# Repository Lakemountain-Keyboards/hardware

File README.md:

<div align="center">

  # Lakemountain Keyboards

  Hardware Repository

  Kicad Schematic & PCB layout

</div>

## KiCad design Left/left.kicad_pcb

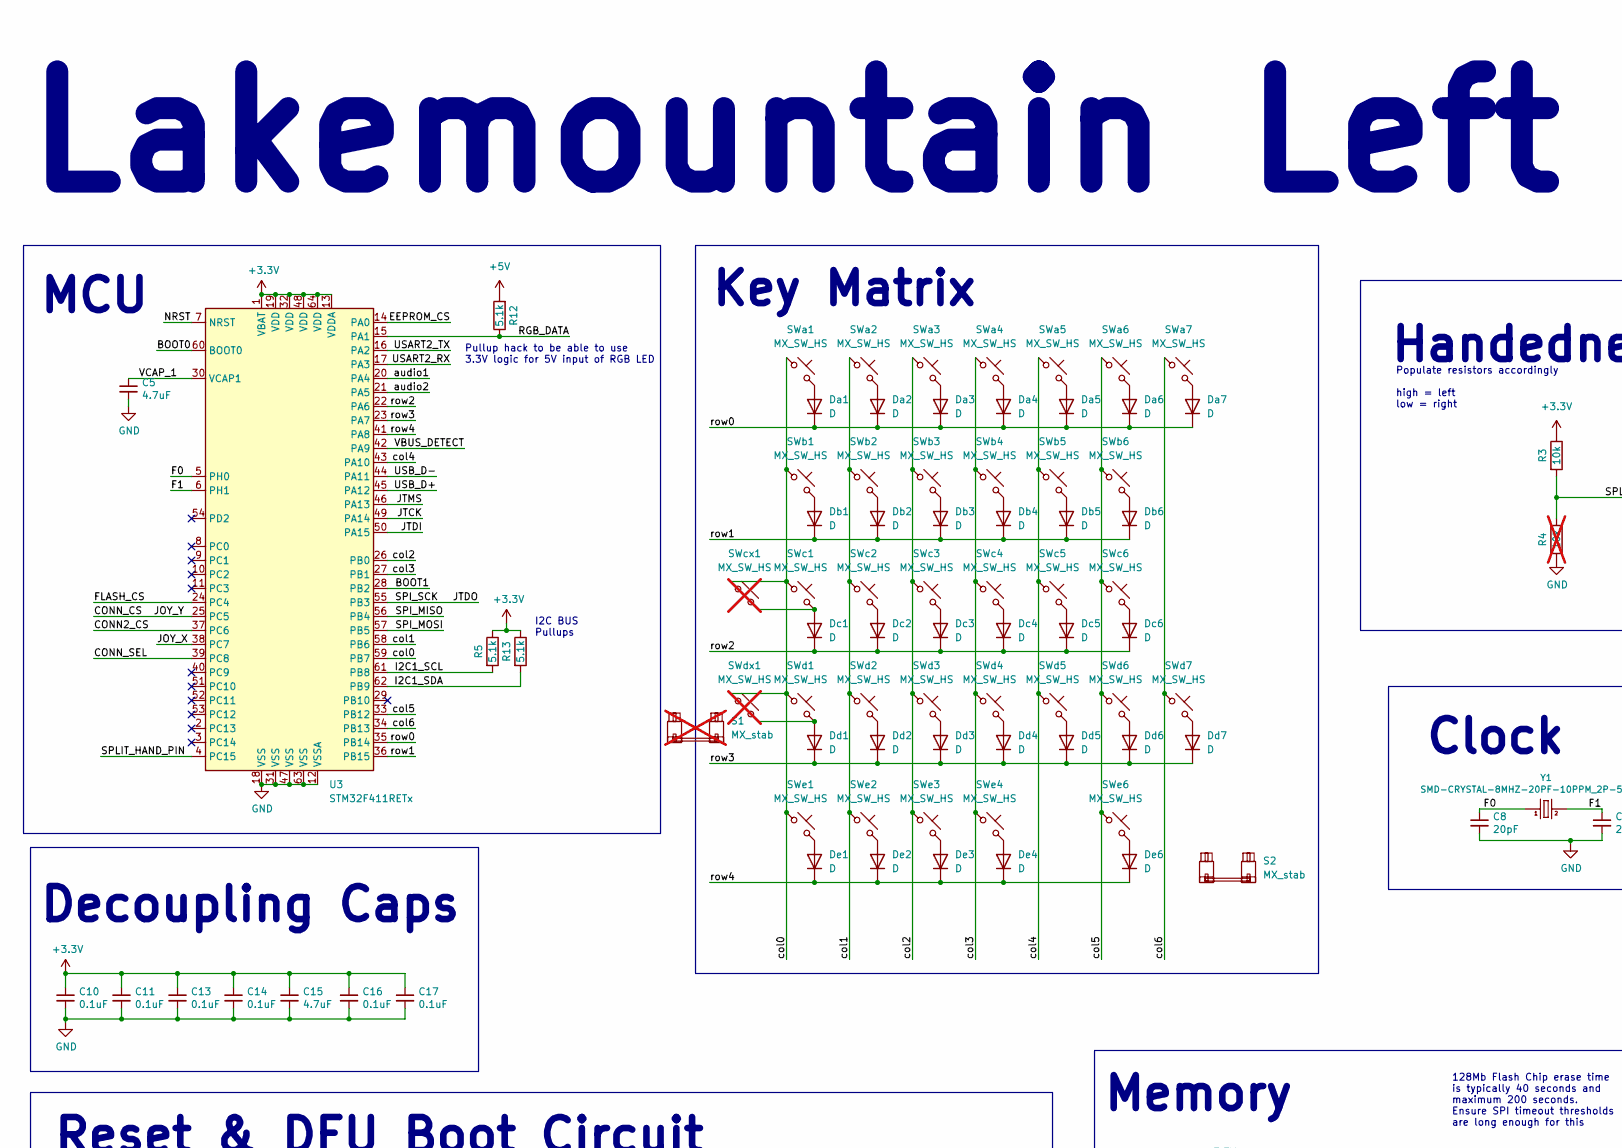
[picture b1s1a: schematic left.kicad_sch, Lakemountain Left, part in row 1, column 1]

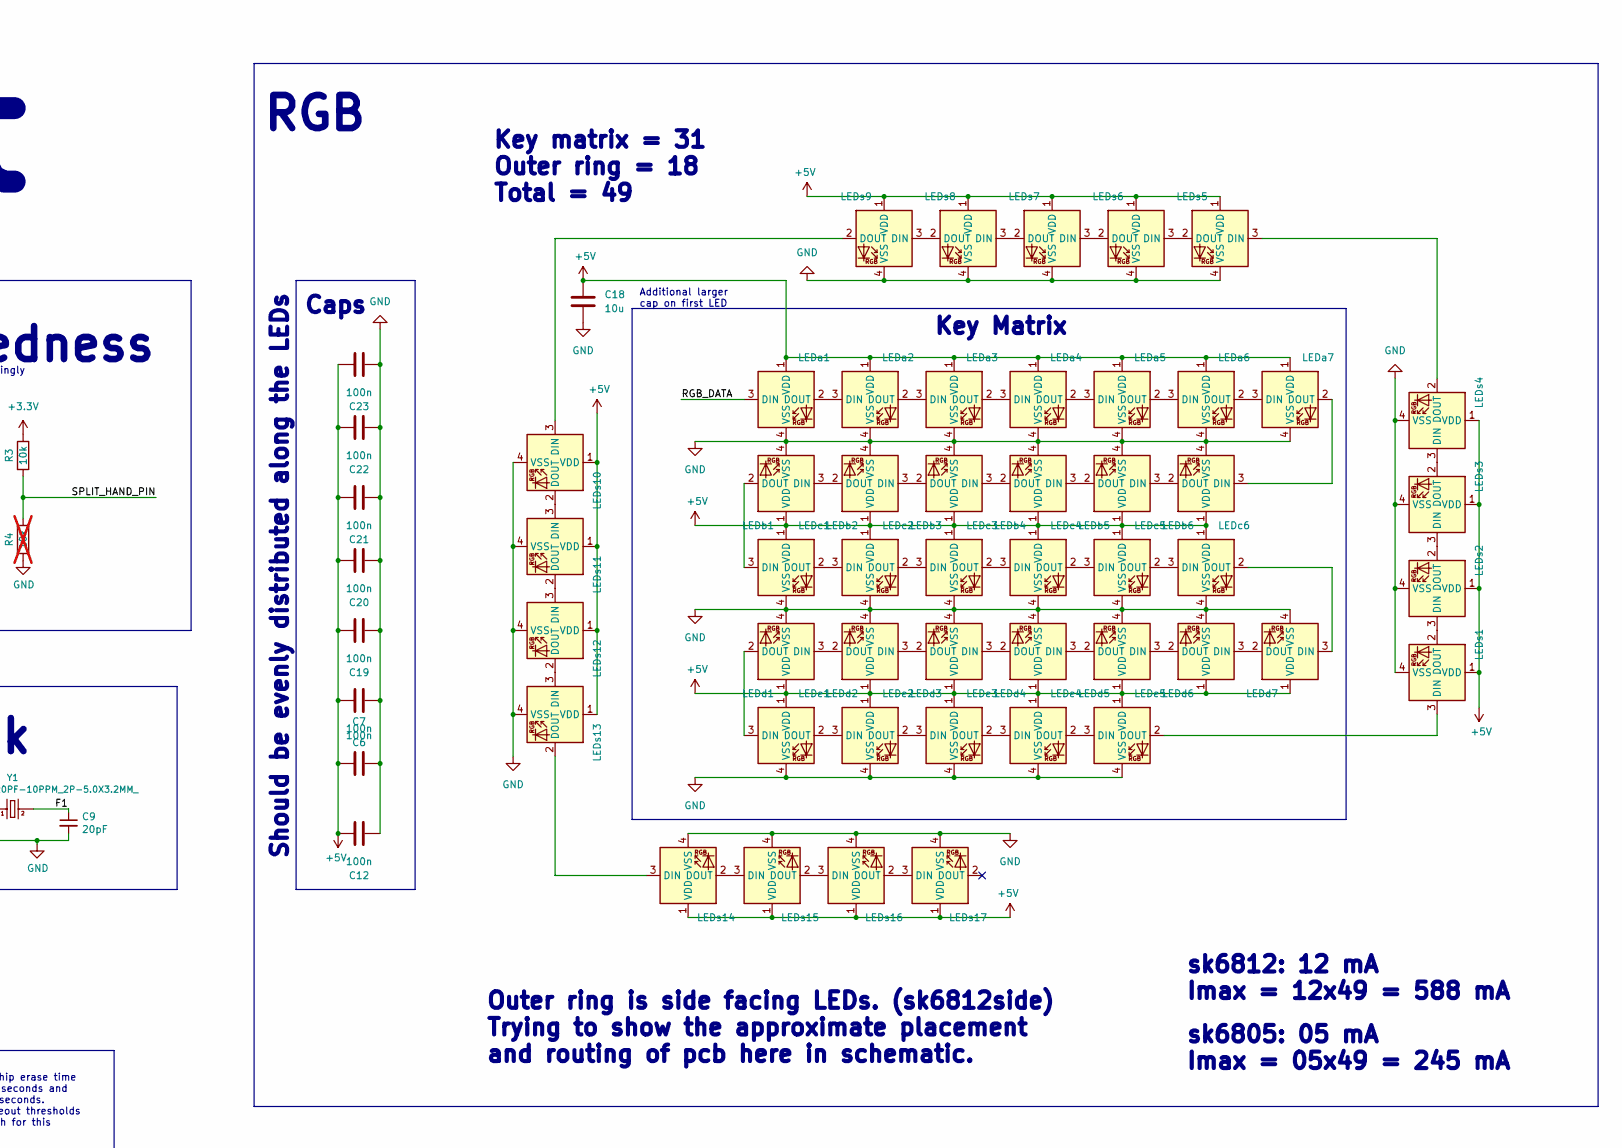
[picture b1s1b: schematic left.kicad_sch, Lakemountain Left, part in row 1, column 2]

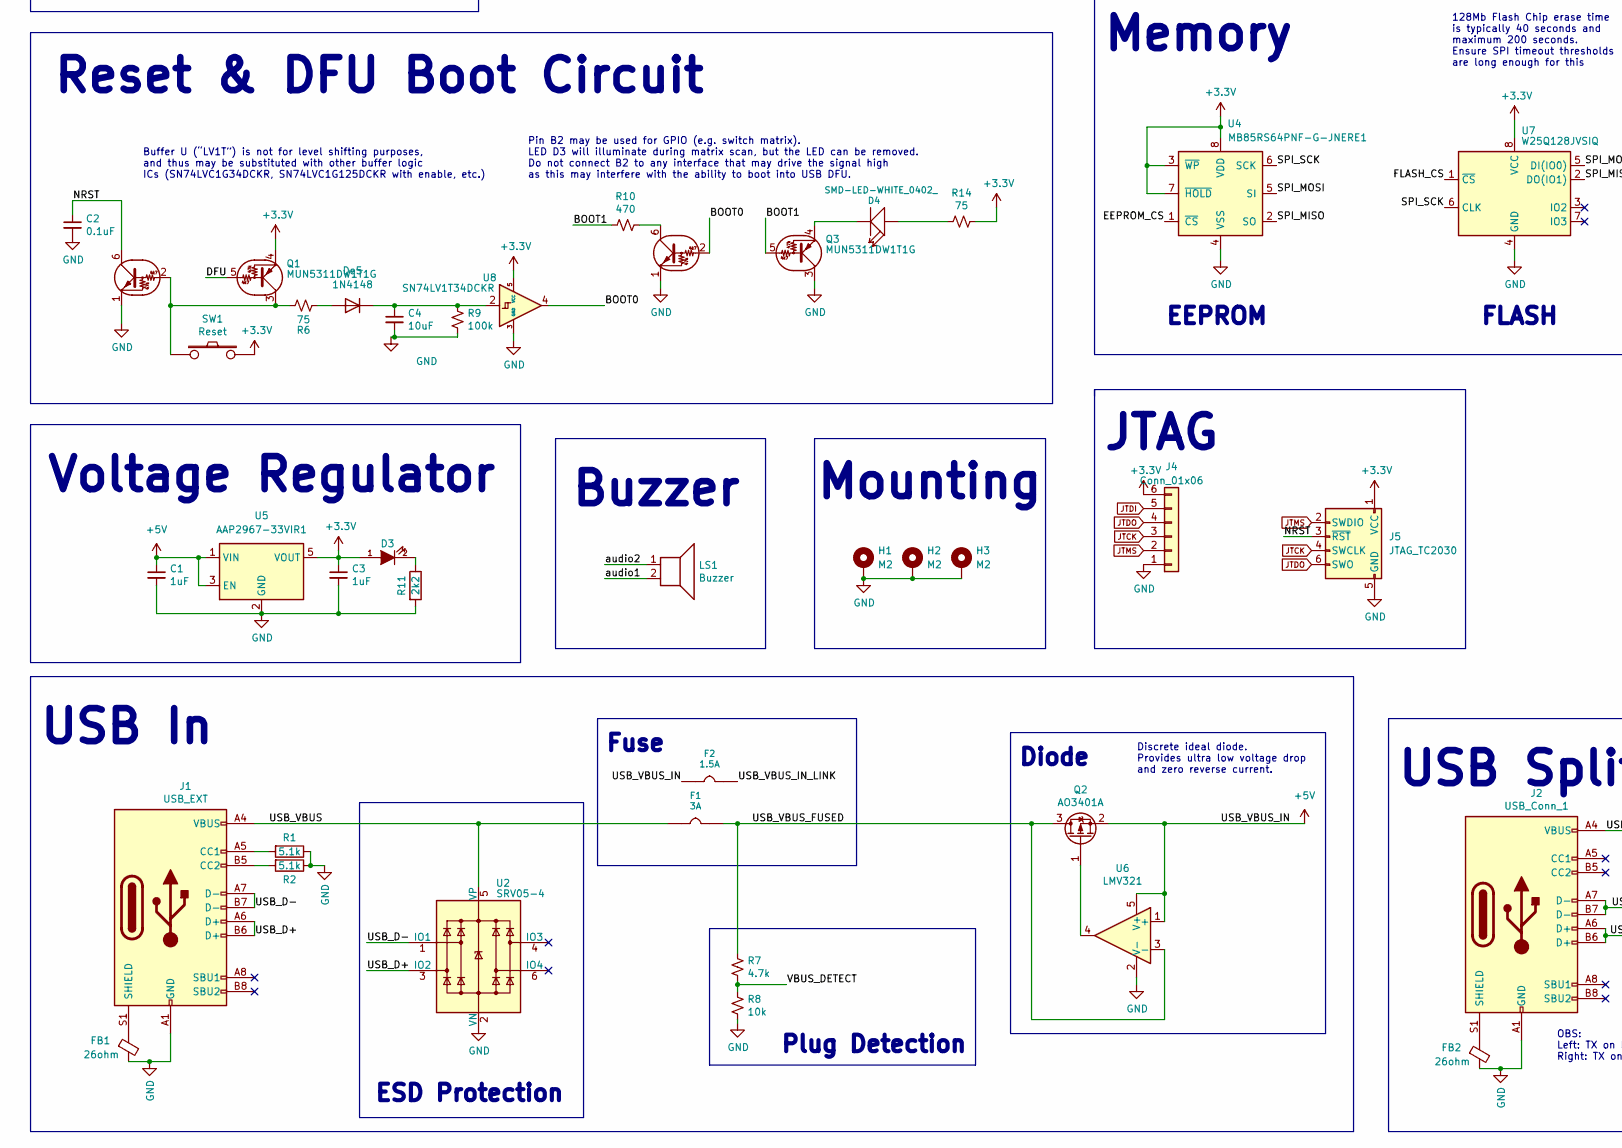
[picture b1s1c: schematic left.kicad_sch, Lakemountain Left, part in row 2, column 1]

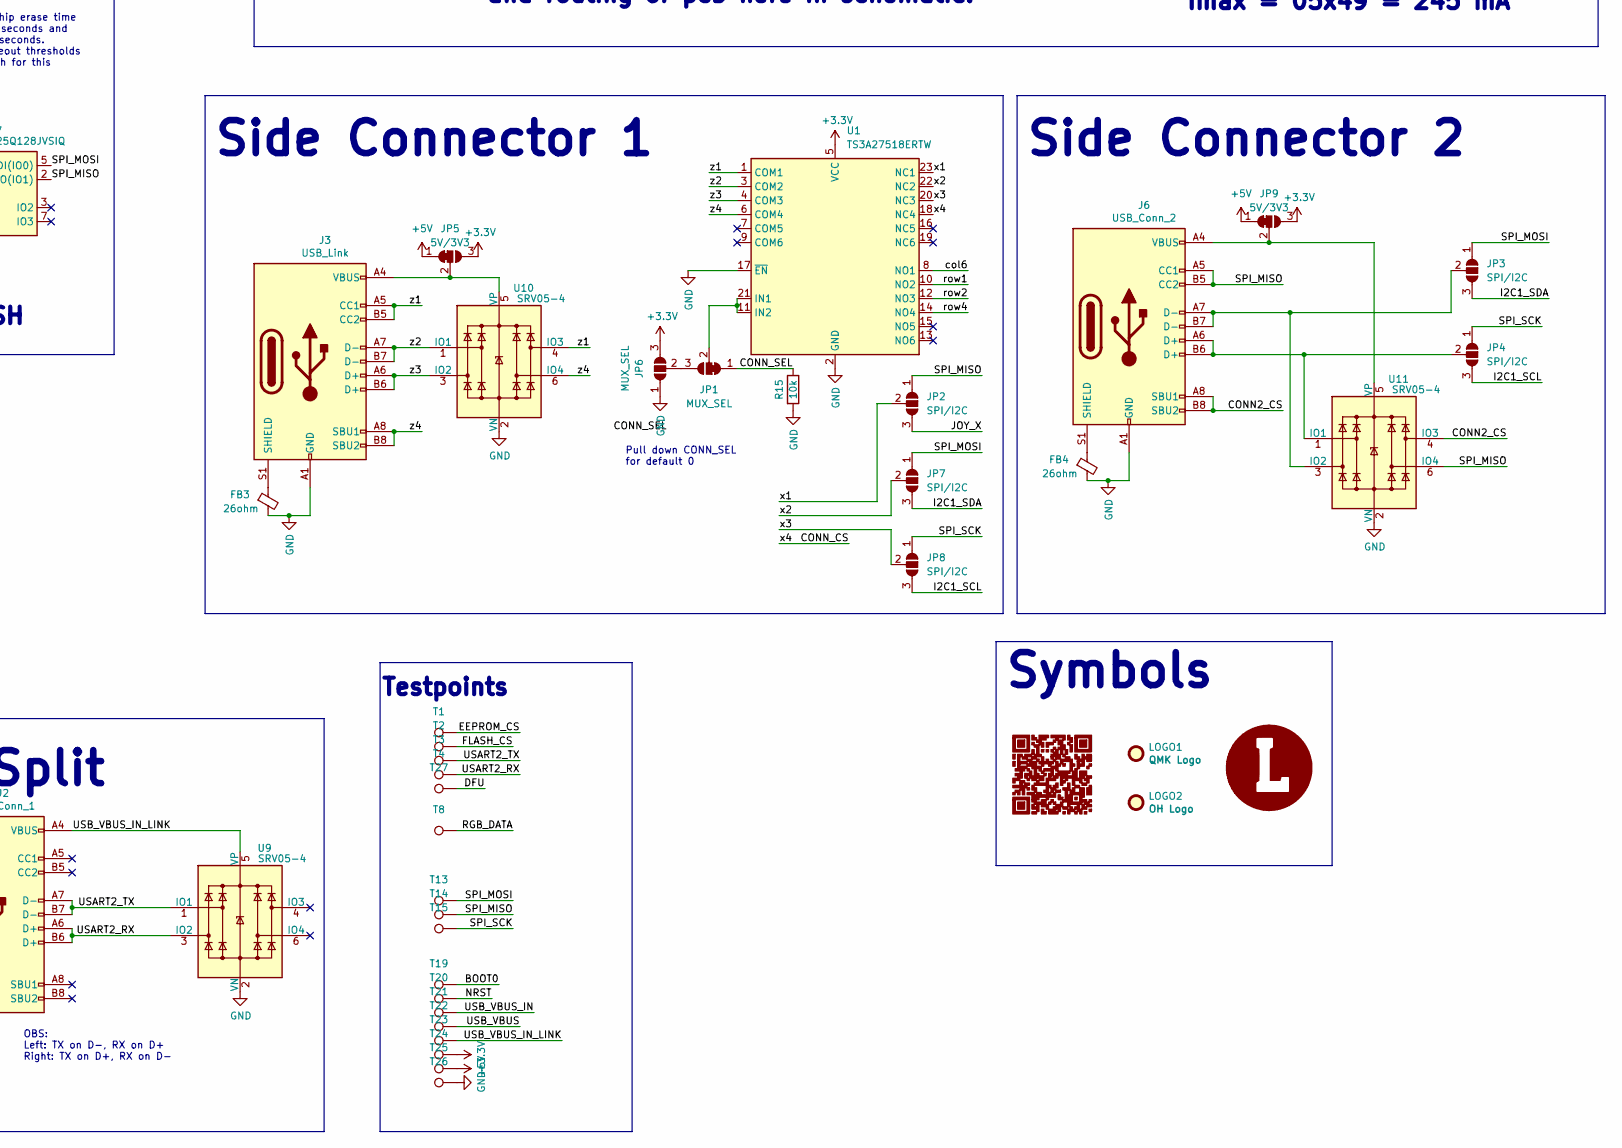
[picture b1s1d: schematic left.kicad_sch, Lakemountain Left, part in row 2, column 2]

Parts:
C1, C3: cap_1uF_10v_0402; C_0402_1005Metric; MPN CC0402KRX5R6BB105; LCSC C52923
C2, C10, C11, C13, C14, C16, C17: cap_100nF_16v_0402; C_0402_1005Metric; MPN CL05B104KO5NNNC; LCSC C1525
C4: cap_10uF_10v_0402; C_0402_1005Metric; MPN CL10A106KP8NNNC; LCSC C19702
C5, C15: cap_4.7uF_10v_0402; C_0402_1005Metric; MPN CL05A475MP5NRNC; LCSC C23733
C6, C7, C12, C19, C20, C21, C22, C23: 100n; C_0805; LCSC C495959
C8, C9: cap_20pF_50v_0402; C_0402_1005Metric; MPN 0402CG200J500NT; LCSC C1554
C18: 10u; C_0805; LCSC C90544
D3: LED; LED_0603_1608Metric; LCSC Part C72041
D4: SMD-LED-WHITE_0402_; LED_0402; MPN 16-219A/T2D-AR2T1QY/3T; LCSC C74342
Da1, Da2, Da3, Da4, Da5, Da6, Da7: D; D_SOD-123; LCSC C81598
Db1, Db2, Db3, Db4, Db5, Db6: D; D_SOD-123; LCSC C81598
Dc1, Dc2, Dc3, Dc4, Dc5, Dc6: D; D_SOD-123; LCSC C81598
Dd1, Dd2, Dd3, Dd4, Dd5, Dd6, Dd7: D; D_SOD-123; LCSC C81598
De1, De2, De3, De4, De6: D; D_SOD-123; LCSC C81598
De5: 1N4148; D_SOD-523; LCSC C68948
F1: 3A; F1206; MPN SMD0805-050; LCSC C89656
F2: 1.5A; F1206; MPN SMD0805-050; LCSC C89655
FB1, FB2, FB3, FB4: fb_0402_26ohm; R_0402_1005Metric; MPN CBG100505U260T; LCSC C668229
H1, H2, H3: M2; MountingHole_2.2mm_M2_Pad_Via
J1: USB_EXT; USB_C_Receptacle_HRO_TYPE-C-31-M-12; Mouser C165948
J2: USB_Conn_1; USB_C_Receptacle_HRO_TYPE-C-31-M-12; Mouser C165948
J3: USB_Link; USB_C_Receptacle_HRO_TYPE-C-31-M-12; Mouser C165948
J4: Conn_01x06; PinHeader_1x06_P2.54mm_Vertical
J5: JTAG_TC2030; CON_TC2030_outlined
J6: USB_Conn_2; USB_C_Receptacle_HRO_TYPE-C-31-M-12; Mouser C165948
JP1: MUX_SEL; SolderJumper-3_P1.3mm_Bridged12_RoundedPad1.0x1.5mm
JP2, JP3, JP4, JP7, JP8: SPI/I2C; SolderJumper-3_P1.3mm_Open_RoundedPad1.0x1.5mm_NumberLabels
JP5, JP9: 5V/3V3; SolderJumper-3_P1.3mm_Bridged12_RoundedPad1.0x1.5mm
JP6: MUX_SEL; SolderJumper-3_P1.3mm_Open_RoundedPad1.0x1.5mm_NumberLabels
LEDa1, LEDa2, LEDa3, LEDa4, LEDa5, LEDa6, LEDa7: MX_SK6812MINI-E; LED_MX_6028R; LCSC C5149201
LEDb1, LEDb2, LEDb3, LEDb4, LEDb5, LEDb6: MX_SK6812MINI-E; LED_MX_6028R_Flipped; LCSC C5149201
LEDc1: MX_SK6812MINI-E; LED_MX_6028R_SOLO; LCSC C5149201
LEDc2, LEDc3, LEDc4, LEDc5, LEDc6: MX_SK6812MINI-E; LED_MX_6028R; LCSC C5149201
LEDd1, LEDd2: MX_SK6812MINI-E; LED_MX_6028R_SOLO; LCSC C5149201
LEDd3, LEDd4, LEDd5, LEDd6, LEDd7: MX_SK6812MINI-E; LED_MX_6028R_Flipped; LCSC C5149201
LEDe1, LEDe2, LEDe3, LEDe4, LEDe5: MX_SK6812MINI-E; LED_MX_6028R; LCSC C5149201
LEDs1, LEDs2, LEDs3, LEDs4, LEDs5, LEDs6, LEDs7, LEDs8, LEDs9, LEDs10, LEDs11, LEDs12, LEDs13, LEDs14, LEDs15, LEDs16, LEDs17: sk6812side; LCSC C2890037
LOGO1: QMK Logo; QMK_PoweredBy
LOGO2: OH Logo; OSHW-Logo2_9.8x8mm_SilkScreen
LS1: Buzzer; Buzzer_Mallory_AST1109MLTRQ; LCSC C201047
Q1, Q3: MUN5311DW1T1G; SOT-363_SC-70-6_SC-88; LCSC C152542
Q2: AO3401A; SOT-23; LCSC Part C15127
R1, R2, R5, R13: 5.1k; R_0603_1608Metric; Mouser C27834
R3, R15: 10k; R_0603_1608Metric; LCSC C25804
R4: 10k; R_0603_1608Metric; LCSC C25804; not fitted
R6, R14: r_75_0402_1p; R_0402_1005Metric; MPN 0402WGF750JTCE; LCSC C25133
R7: r_4.7k_0402_1p; R_0402_1005Metric; MPN 0402WGF4701TCE; LCSC C25900
R8: r_10k_0402_1p; R_0402_1005Metric; MPN 0402WGF1002TCE; LCSC C25744
R9: r_100k_0402_1p; R_0402_1005Metric; MPN 0402WGF1003TCE; LCSC C25741
R10: r_470_0402_1p; R_0402_1005Metric; MPN 0402WGF4700TCE; LCSC C25117
R11: 2k2; R_0603_1608Metric; LCSC C4190
R12: 5.1k; R_0805_2012Metric_Pad1.20x1.40mm_HandSolder; Mouser C27834
S1: MX_stab; STAB_MX_P_2.25u; JLCPCB BOM 0; not fitted
S2: MX_stab; STAB_MX_P_2.25u; JLCPCB BOM 0
SW1: Reset; SW_SPST_TL3342; Mouser C318884
SWa1, SWa2, SWa3, SWa4, SWa5, SWa6, SWa7: MX_SW_HS; SW_MX_HS_1u; LCSC C2803348
SWb1: MX_SW_HS; SW_MX_HS_1.5u; LCSC C2803348
SWb2, SWb3, SWb4, SWb5, SWb6: MX_SW_HS; SW_MX_HS_1u; LCSC C2803348
SWc1: MX_SW_HS; SW_MX_HS_1.75u; LCSC C2803348
SWc2, SWc3, SWc4, SWc5, SWc6: MX_SW_HS; SW_MX_HS_1u; LCSC C2803348
SWcx1: MX_SW_HS; SW_MX_HS_1.75u_stp; LCSC C2803348; not fitted
SWd1: MX_SW_HS; SW_MX_HS_1.25u; LCSC C2803348
SWd2, SWd3, SWd4, SWd5, SWd6, SWd7: MX_SW_HS; SW_MX_HS_1u; LCSC C2803348
SWdx1: MX_SW_HS; SW_MX_HS_2.25u; LCSC C2803348; not fitted
SWe1, SWe2, SWe3, SWe4: MX_SW_HS; SW_MX_HS_1.25u; LCSC C2803348
SWe6: MX_SW_HS; SW_MX_HS_2.25u; LCSC C2803348
T1, T2, T3, T4, T8, T13, T14, T15, T19, T20, T21, T22, T23: TP; TestPoint_Pad_D1.0mm
T24: 3V3; TestPoint_Pad_D1.0mm
T25: 5V; TestPoint_Pad_D1.0mm
T26, T27: GND; TestPoint_Pad_D1.0mm
U1: TS3A27518ERTW; WQFN-24-1EP_4x4mm_P0.5mm_EP2.6x2.6mm; LCSC C2651937
U2, U9, U10, U11: SRV05-4; SOT-23-6; LCSC C85364
U3: STM32F411RETx; LQFP-64_10x10mm_P0.5mm
U4: MB85RS64PNF-G-JNERE1; SOP-8_3.9x4.9mm_P1.27mm; LCSC C8741
U5: AAP2967-33VIR1; SOT-23-5; LCSC C370742
U6: LMV321; SOT-23-5; JLCPCB BOM 1
U7: W25Q128JVSIQ; SOIC-8_5.23x5.23mm_P1.27mm; LCSC C97521
U8: SN74LV1T34DCKR; SOT-353_SC-70-5; LCSC C78541
Y1: SMD-CRYSTAL-8MHZ-20PF-10PPM_2P-5.0X3.2MM_; X2-SMD-5.0X3.2X1.3MM; MPN X50328MSB2GI; LCSC C115962

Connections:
+3.3V: C3.1, C10.1, C11.1, C13.1, C14.1, C15.1, C16.1, C17.1, D3.1 (A), J4.6, J5.1 (VCC), JP5.3 (B), JP6.3 (B), JP9.3 (B), Q1.4 (E), R3.1, R5.1, R13.1, R14.1, SW1.2, T24.1, U1.5 (VCC), U3.1 (VBAT), U3.13 (VDDA), U3.19 (VDD), U3.32 (VDD), U3.48 (VDD), U3.64 (VDD), U4.3 (~WP), U4.7 (~HOLD), U4.8 (VDD), U5.5 (VOUT), U7.8 (VCC), U8.5 (VCC)
+5V: C1.1, C6.1, C7.1, C12.1, C18.1, C19.1, C20.2, C21.1, C22.2, C23.1, F2.2, JP5.1 (A), JP9.1 (A), LEDa1.1 (VDD), LEDa2.1 (VDD), LEDa3.1 (VDD), LEDa4.1 (VDD), LEDa5.1 (VDD), LEDa6.1 (VDD), LEDa7.1 (VDD), LEDb1.1 (VDD), LEDb2.1 (VDD), LEDb3.1 (VDD), LEDb4.1 (VDD), LEDb5.1 (VDD), LEDb6.1 (VDD), LEDc1.1 (VDD), LEDc2.1 (VDD), LEDc3.1 (VDD), LEDc4.1 (VDD), LEDc5.1 (VDD), LEDc6.1 (VDD), LEDd1.1 (VDD), LEDd2.1 (VDD), LEDd3.1 (VDD), LEDd4.1 (VDD), LEDd5.1 (VDD), LEDd6.1 (VDD), LEDd7.1 (VDD), LEDe1.1 (VDD), LEDe2.1 (VDD), LEDe3.1 (VDD), LEDe4.1 (VDD), LEDe5.1 (VDD), LEDs1.1 (VDD), LEDs2.1 (VDD), LEDs3.1 (VDD), LEDs4.1 (VDD), LEDs5.1 (VDD), LEDs6.1 (VDD), LEDs7.1 (VDD), LEDs8.1 (VDD), LEDs9.1 (VDD), LEDs10.1 (VDD), LEDs11.1 (VDD), LEDs12.1 (VDD), LEDs13.1 (VDD), LEDs14.1 (VDD), LEDs15.1 (VDD), LEDs16.1 (VDD), LEDs17.1 (VDD), Q2.2 (S), R12.2, T21.1, T25.1, U5.1 (VIN), U5.3 (EN), U6.1 (+), U6.5 (V+)
/BOOT0: Q3.2 (B), T19.1, U3.60 (BOOT0), U8.4
/BOOT1: Q3.5, R10.2, U3.28 (PB2)
/CONN2_CS: J6.A8 (SBU1), J6.B8 (SBU2), U3.37 (PC6), U11.4 (IO3)
/CONN_CS: U1.18 (NC4), U3.25 (PC5)
/CONN_SEL: JP1.1 (A), R15.1, U3.39 (PC8)
/DFU: Q1.5, T27.1
/EEPROM_CS: T1.1, U3.14 (PA0), U4.1 (~CS)
/F0: C8.1, U3.5 (PH0), Y1.1
/F1: C9.1, U3.6 (PH1), Y1.2
/FLASH_CS: T2.1, U3.24 (PC4), U7.1 (~CS)
/I2C1_SCL: JP4.3 (B), JP8.3 (B), R5.2, U3.61 (PB8)
/I2C1_SDA: JP3.3 (B), JP7.3 (B), R13.2, U3.62 (PB9)
/JOY_X: JP2.3 (B), U3.38 (PC7)
/NRST: C2.1, J5.3 (~RST), Q1.6 (C), T20.1, U3.7 (NRST)
/RGB_DATA: LEDa1.3 (DIN), R12.1, T8.1, U3.15 (PA1)
/SPI_MISO: J6.A5 (CC1), J6.B5 (CC2), JP2.1 (A), T14.1, U3.56 (PB4), U4.2 (SO), U7.2 (DO(IO1)), U11.6 (IO4)
/SPI_MOSI: JP3.1 (A), JP7.1 (A), T13.1, U3.57 (PB5), U4.5 (SI), U7.5 (DI(IO0))
/SPLIT_HAND_PIN: R3.2, R4.1, U3.4 (PC15)
/USART2_RX: J2.A6 (D+), J2.B6 (D+), T4.1, U3.17 (PA3), U9.3 (IO2)
/USART2_TX: J2.A7 (D-), J2.B7 (D-), T3.1, U3.16 (PA2), U9.1 (IO1)
/USB_D+: J1.A6 (D+), J1.B6 (D+), U2.3 (IO2), U3.45 (PA12)
/USB_D-: J1.A7 (D-), J1.B7 (D-), U2.1 (IO1), U3.44 (PA11)
/USB_VBUS: F1.2, J1.A4 (VBUS), J1.A9 (VBUS), J1.B4 (VBUS), J1.B9 (VBUS), T22.1, U2.5 (VP)
/USB_VBUS_FUSED: F1.1, Q2.3 (D), R7.1, U6.3 (-)
/USB_VBUS_IN_LINK: F2.1, J2.A4 (VBUS), J2.A9 (VBUS), J2.B4 (VBUS), J2.B9 (VBUS), T23.1, U9.5 (VP)
/VBUS_DETECT: R7.2, R8.1, U3.42 (PA9)
/VCAP_1: C5.1, U3.30 (VCAP1)
/audio1: LS1.2, U3.20 (PA4)
/audio2: LS1.1, U3.21 (PA5)
/col0: SWa1.1, SWb1.1, SWc1.1, SWcx1.1, SWd1.1, SWdx1.1, SWe1.1, U3.59 (PB7)
/col1: SWa2.1, SWb2.1, SWc2.1, SWd2.1, SWe2.1, U3.58 (PB6)
/col2: SWa3.1, SWb3.1, SWc3.1, SWd3.1, SWe3.1, U3.26 (PB0)
/col3: SWa4.1, SWb4.1, SWc4.1, SWd4.1, SWe4.1, U3.27 (PB1)
/col4: SWa5.1, SWb5.1, SWc5.1, SWd5.1, U3.43 (PA10)
/col5: SWa6.1, SWb6.1, SWc6.1, SWd6.1, SWe6.1, U3.33 (PB12)
/col6: SWa7.1, SWd7.1, U1.8 (NO1), U3.34 (PB13)
/row0: Da1.1 (K), Da2.1 (K), Da3.1 (K), Da4.1 (K), Da5.1 (K), Da6.1 (K), Da7.1 (K), U3.35 (PB14)
/row1: Db1.1 (K), Db2.1 (K), Db3.1 (K), Db4.1 (K), Db5.1 (K), Db6.1 (K), U1.10 (NO2), U3.36 (PB15)
/row2: Dc1.1 (K), Dc2.1 (K), Dc3.1 (K), Dc4.1 (K), Dc5.1 (K), Dc6.1 (K), U1.12 (NO3), U3.22 (PA6)
/row3: Dd1.1 (K), Dd2.1 (K), Dd3.1 (K), Dd4.1 (K), Dd5.1 (K), Dd6.1 (K), Dd7.1 (K), U3.23 (PA7)
/row4: De1.1 (K), De2.1 (K), De3.1 (K), De4.1 (K), De6.1 (K), U1.14 (NO4), U3.41 (PA8)
/x1: JP2.2 (C), U1.23 (NC1)
/x2: JP7.2 (C), U1.22 (NC2)
/x3: JP8.2 (C), U1.20 (NC3)
/z1: J3.A5 (CC1), J3.B5 (CC2), U1.1 (COM1), U10.4 (IO3)
/z2: J3.A7 (D-), J3.B7 (D-), U1.3 (COM2), U10.1 (IO1)
/z3: J3.A6 (D+), J3.B6 (D+), U1.4 (COM3), U10.3 (IO2)
/z4: J3.A8 (SBU1), J3.B8 (SBU2), U1.6 (COM4), U10.6 (IO4)
GND: C1.2, C2.2, C3.2, C4.2, C5.2, C6.2, C7.2, C8.2, C9.2, C10.2, C11.2, C12.2, C13.2, C14.2, C15.2, C16.2, C17.2, C18.2, C19.2, C20.1, C21.2, C22.1, C23.2, FB1.2, FB2.2, FB3.2, FB4.2, H1.1, H2.1, H3.1, J1.A1 (GND), J1.A12 (GND), J1.B1 (GND), J1.B12 (GND), J2.A1 (GND), J2.A12 (GND), J2.B1 (GND), J2.B12 (GND), J3.A1 (GND), J3.A12 (GND), J3.B1 (GND), J3.B12 (GND), J4.1, J5.5 (GND), J6.A1 (GND), J6.A12 (GND), J6.B1 (GND), J6.B12 (GND), JP6.1 (A), LEDa1.4 (VSS), LEDa2.4 (VSS), LEDa3.4 (VSS), LEDa4.4 (VSS), LEDa5.4 (VSS), LEDa6.4 (VSS), LEDa7.4 (VSS), LEDb1.4 (VSS), LEDb2.4 (VSS), LEDb3.4 (VSS), LEDb4.4 (VSS), LEDb5.4 (VSS), LEDb6.4 (VSS), LEDc1.4 (VSS), LEDc2.4 (VSS), LEDc3.4 (VSS), LEDc4.4 (VSS), LEDc5.4 (VSS), LEDc6.4 (VSS), LEDd1.4 (VSS), LEDd2.4 (VSS), LEDd3.4 (VSS), LEDd4.4 (VSS), LEDd5.4 (VSS), LEDd6.4 (VSS), LEDd7.4 (VSS), LEDe1.4 (VSS), LEDe2.4 (VSS), LEDe3.4 (VSS), LEDe4.4 (VSS), LEDe5.4 (VSS), LEDs1.4 (VSS), LEDs2.4 (VSS), LEDs3.4 (VSS), LEDs4.4 (VSS), LEDs5.4 (VSS), LEDs6.4 (VSS), LEDs7.4 (VSS), LEDs8.4 (VSS), LEDs9.4 (VSS), LEDs10.4 (VSS), LEDs11.4 (VSS), LEDs12.4 (VSS), LEDs13.4 (VSS), LEDs14.4 (VSS), LEDs15.4 (VSS), LEDs16.4 (VSS), LEDs17.4 (VSS), Q1.1 (E), Q3.1 (E), Q3.3 (C), R1.1, R2.1, R4.2, R8.2, R9.2, R11.2, R15.2, T26.1, U1.2 (GND), U1.17 (~EN), U1.25 (GND), U2.2 (VN), U3.12 (VSSA), U3.18 (VSS), U3.31 (VSS), U3.47 (VSS), U3.63 (VSS), U4.4 (VSS), U5.2 (GND), U6.2 (V-), U7.4 (GND), U8.3 (GND), U9.2 (VN), U10.2 (VN), U11.2 (VN)
JTCK: J4.3, J5.4 (SWCLK), U3.49 (PA14)
JTDI: J4.5, U3.50 (PA15)
JTDO: J4.4, J5.6 (SWO), JP4.1 (A), JP8.1 (A), T15.1, U3.55 (PB3), U4.6 (SCK), U7.6 (CLK)
JTMS: J4.2, J5.2 (SWDIO), U3.46 (PA13)
unnamed: D3.2 (K), R11.1
unnamed: D4.+, R14.2
unnamed: D4.-, Q3.4 (E)
unnamed: Da1.2 (A), SWa1.2
unnamed: Da2.2 (A), SWa2.2
unnamed: Da3.2 (A), SWa3.2
unnamed: Da4.2 (A), SWa4.2
unnamed: Da5.2 (A), SWa5.2
unnamed: Da6.2 (A), SWa6.2
unnamed: Da7.2 (A), SWa7.2
unnamed: Db1.2 (A), SWb1.2
unnamed: Db2.2 (A), SWb2.2
unnamed: Db3.2 (A), SWb3.2
unnamed: Db4.2 (A), SWb4.2
unnamed: Db5.2 (A), SWb5.2
unnamed: Db6.2 (A), SWb6.2
unnamed: Dc1.2 (A), SWc1.2, SWcx1.2
unnamed: Dc2.2 (A), SWc2.2
unnamed: Dc3.2 (A), SWc3.2
unnamed: Dc4.2 (A), SWc4.2
unnamed: Dc5.2 (A), SWc5.2
unnamed: Dc6.2 (A), SWc6.2
unnamed: Dd1.2 (A), SWd1.2, SWdx1.2
unnamed: Dd2.2 (A), SWd2.2
unnamed: Dd3.2 (A), SWd3.2
unnamed: Dd4.2 (A), SWd4.2
unnamed: Dd5.2 (A), SWd5.2
unnamed: Dd6.2 (A), SWd6.2
unnamed: Dd7.2 (A), SWd7.2
unnamed: De1.2 (A), SWe1.2
unnamed: De2.2 (A), SWe2.2
unnamed: De3.2 (A), SWe3.2
unnamed: De4.2 (A), SWe4.2
unnamed: De5.2 (A), R6.2
unnamed: C4.1, De5.1 (K), R9.1, U8.2
unnamed: De6.2 (A), SWe6.2
unnamed: J1.A5 (CC1), R1.2
unnamed: J1.B5 (CC2), R2.2
unnamed: FB1.1, J1.S1 (SHIELD)
unnamed: FB2.1, J2.S1 (SHIELD)
unnamed: FB3.1, J3.S1 (SHIELD)
unnamed: FB4.1, J6.S1 (SHIELD)
unnamed: JP1.3 (B), JP6.2 (C)
unnamed: JP1.2 (C), U1.11 (IN2), U1.21 (IN1)
unnamed: J6.A7 (D-), J6.B7 (D-), JP3.2 (C), U11.3 (IO2)
unnamed: J6.A6 (D+), J6.B6 (D+), JP4.2 (C), U11.1 (IO1)
unnamed: J3.A4 (VBUS), J3.A9 (VBUS), J3.B4 (VBUS), J3.B9 (VBUS), JP5.2 (C), U10.5 (VP)
unnamed: J6.A4 (VBUS), J6.A9 (VBUS), J6.B4 (VBUS), J6.B9 (VBUS), JP9.2 (C), U11.5 (VP)
unnamed: LEDa1.2 (DOUT), LEDa2.3 (DIN)
unnamed: LEDa2.2 (DOUT), LEDa3.3 (DIN)
unnamed: LEDa3.2 (DOUT), LEDa4.3 (DIN)
unnamed: LEDa4.2 (DOUT), LEDa5.3 (DIN)
unnamed: LEDa5.2 (DOUT), LEDa6.3 (DIN)
unnamed: LEDa6.2 (DOUT), LEDa7.3 (DIN)
unnamed: LEDa7.2 (DOUT), LEDb6.3 (DIN)
unnamed: LEDb1.3 (DIN), LEDb2.2 (DOUT)
unnamed: LEDb1.2 (DOUT), LEDc1.3 (DIN)
unnamed: LEDb2.3 (DIN), LEDb3.2 (DOUT)
unnamed: LEDb3.3 (DIN), LEDb4.2 (DOUT)
unnamed: LEDb4.3 (DIN), LEDb5.2 (DOUT)
unnamed: LEDb5.3 (DIN), LEDb6.2 (DOUT)
unnamed: LEDc1.2 (DOUT), LEDc2.3 (DIN)
unnamed: LEDc2.2 (DOUT), LEDc3.3 (DIN)
unnamed: LEDc3.2 (DOUT), LEDc4.3 (DIN)
unnamed: LEDc4.2 (DOUT), LEDc5.3 (DIN)
unnamed: LEDc5.2 (DOUT), LEDc6.3 (DIN)
unnamed: LEDc6.2 (DOUT), LEDd7.3 (DIN)
unnamed: LEDd1.3 (DIN), LEDd2.2 (DOUT)
unnamed: LEDd1.2 (DOUT), LEDe1.3 (DIN)
unnamed: LEDd2.3 (DIN), LEDd3.2 (DOUT)
unnamed: LEDd3.3 (DIN), LEDd4.2 (DOUT)
unnamed: LEDd4.3 (DIN), LEDd5.2 (DOUT)
unnamed: LEDd5.3 (DIN), LEDd6.2 (DOUT)
unnamed: LEDd6.3 (DIN), LEDd7.2 (DOUT)
unnamed: LEDe1.2 (DOUT), LEDe2.3 (DIN)
unnamed: LEDe2.2 (DOUT), LEDe3.3 (DIN)
unnamed: LEDe3.2 (DOUT), LEDe4.3 (DIN)
unnamed: LEDe4.2 (DOUT), LEDe5.3 (DIN)
unnamed: LEDe5.2 (DOUT), LEDs1.3 (DIN)
unnamed: LEDs1.2 (DOUT), LEDs2.3 (DIN)
unnamed: LEDs2.2 (DOUT), LEDs3.3 (DIN)
unnamed: LEDs3.2 (DOUT), LEDs4.3 (DIN)
unnamed: LEDs4.2 (DOUT), LEDs5.3 (DIN)
unnamed: LEDs5.2 (DOUT), LEDs6.3 (DIN)
unnamed: LEDs6.2 (DOUT), LEDs7.3 (DIN)
unnamed: LEDs7.2 (DOUT), LEDs8.3 (DIN)
unnamed: LEDs8.2 (DOUT), LEDs9.3 (DIN)
unnamed: LEDs9.2 (DOUT), LEDs10.3 (DIN)
unnamed: LEDs10.2 (DOUT), LEDs11.3 (DIN)
unnamed: LEDs11.2 (DOUT), LEDs12.3 (DIN)
unnamed: LEDs12.2 (DOUT), LEDs13.3 (DIN)
unnamed: LEDs13.2 (DOUT), LEDs14.3 (DIN)
unnamed: LEDs14.2 (DOUT), LEDs15.3 (DIN)
unnamed: LEDs15.2 (DOUT), LEDs16.3 (DIN)
unnamed: LEDs16.2 (DOUT), LEDs17.3 (DIN)
unnamed: Q1.2 (B), Q1.3 (C), R6.1, SW1.1
unnamed: Q2.1 (G), U6.4
unnamed: Q3.6 (C), R10.1

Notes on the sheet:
128Mb Flash Chip erase time is typically 40 seconds and maximum 200 seconds. Ensure SPI timeout thresholds are long enough for this
Side Connector 1
USB In
Plug Detection
Caps
Memory
Decoupling Caps
I2C BUS Pullups
Handedness
Pull down CONN_SEL for default 0
Pin B2 may be used for GPIO (e.g. switch matrix). LED D3 will illuminate during matrix scan, but the LED can be removed. Do not connect B2 to any interface that may drive the signal high as this may interfere with the ability to boot into USB DFU.
USB Split
ESD Protection
Voltage Regulator
Diode
sk6812: 12 mA Imax = 12x49 = 588 mA
Additional larger cap on first LED
Should be evenly distributed along the LEDs
Clock
EEPROM
Symbols
Discrete ideal diode. Provides ultra low voltage drop and zero reverse current.
Populate resistors accordingly high = left low = right
OBS: Left: TX on D-, RX on D+ Right: TX on D+, RX on D-
MCU
sk6805: 05 mA Imax = 05x49 = 245 mA
Buffer U (“LV1T”) is not for level shifting purposes, and thus may be substituted with other buffer logic ICs (SN74LVC1G34DCKR, SN74LVC1G125DCKR with enable, etc.)
Key Matrix
JTAG
Fuse
Testpoints
Side Connector 2
Outer ring is side facing LEDs. (sk6812side) Trying to show the approximate placement and routing of pcb here in schematic.
Pullup hack to be able to use 3.3V logic for 5V input of RGB LED
Key matrix = 31 Outer ring = 18 Total = 49
FLASH
Mounting
Buzzer
Reset & DFU Boot Circuit
Lakemountain Left

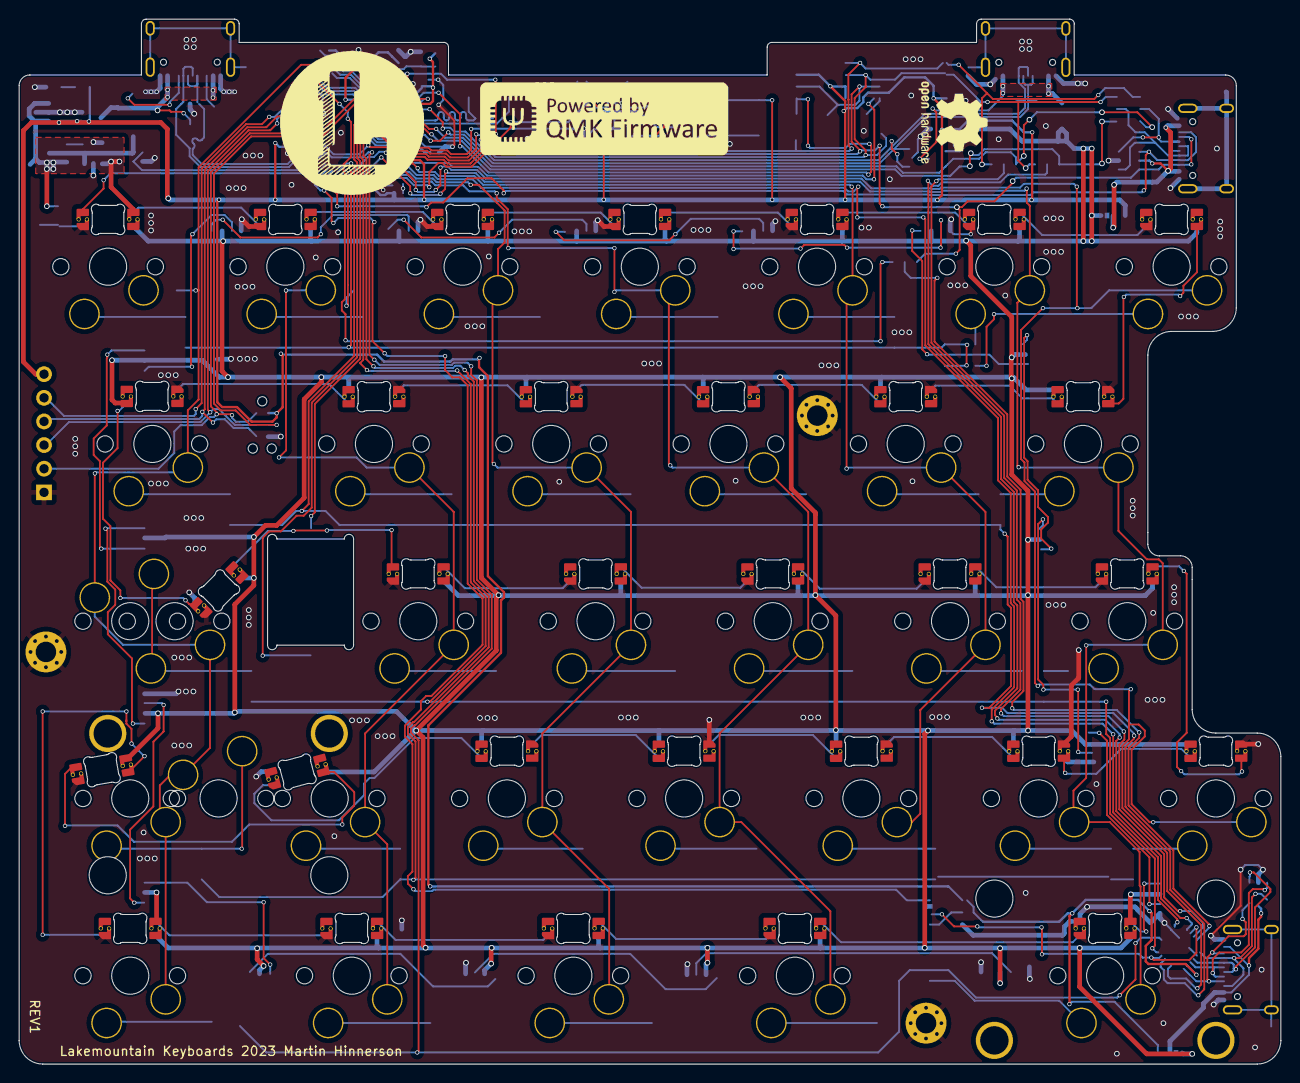
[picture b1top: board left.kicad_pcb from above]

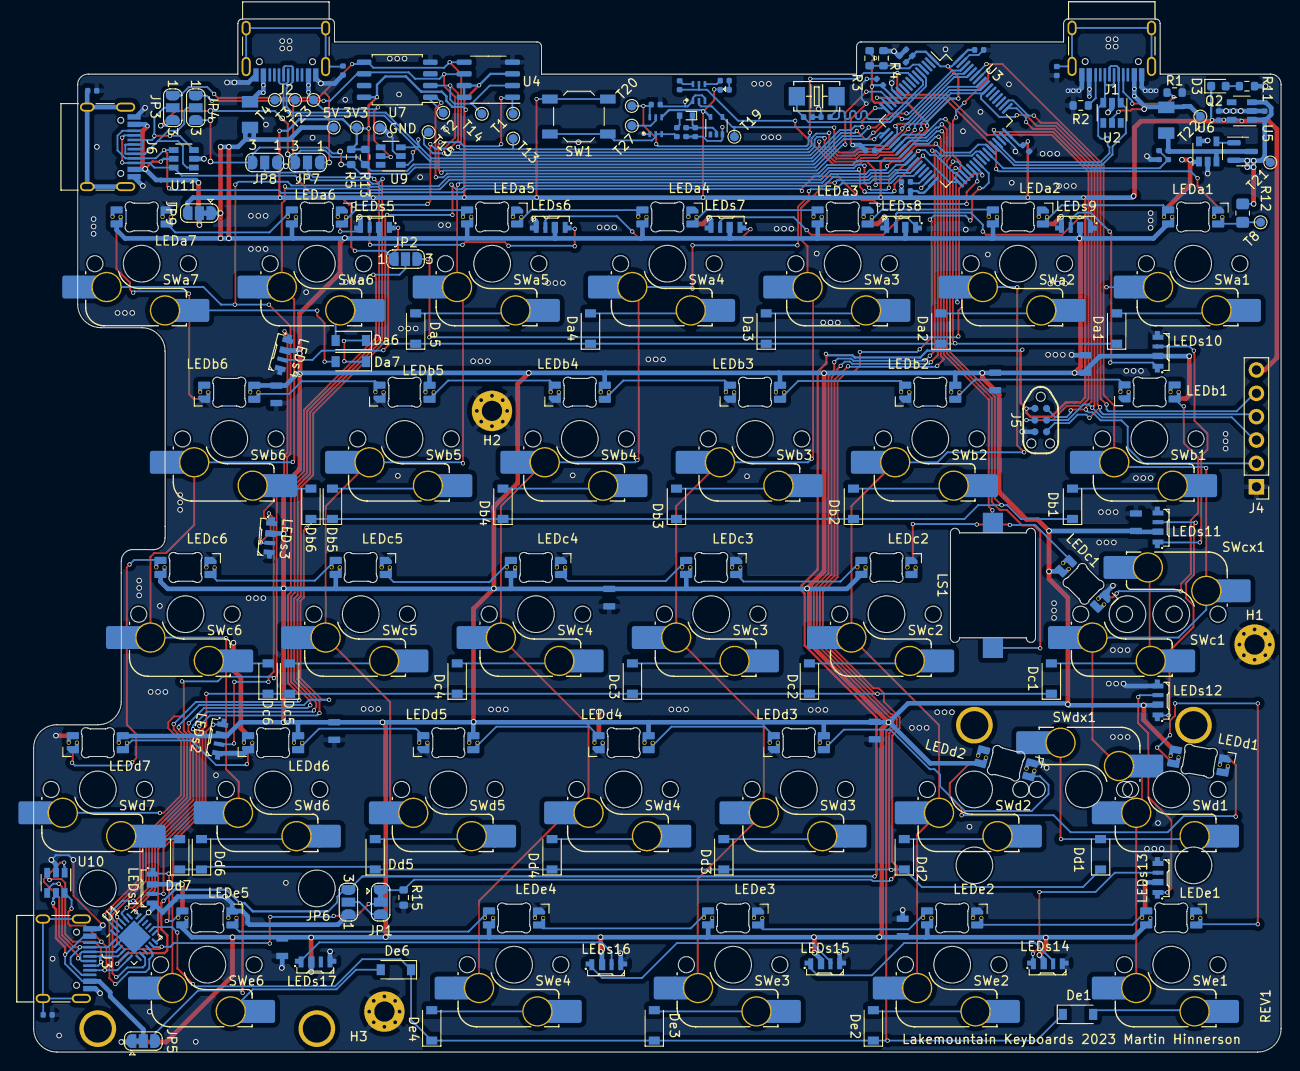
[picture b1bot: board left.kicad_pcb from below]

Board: 2 copper layers, 135.6 x 112.3 mm, 215 parts (211 on the bottom side), 153 nets.

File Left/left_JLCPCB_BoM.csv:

Comment,Designator,Footprint,LCSC
"5.1k","R13,R5,R2,R1","R_0603_1608Metric","C104384"
"SRV05-4","U11,U2,U10,U9","SOT-23-6","C85364"
"10k","R4,R3,R15","R_0603_1608Metric","C25804"
"MX_SK6812MINI-E","LEDb1,LEDd4,LEDd6,LEDb4,LEDb6,LEDb5,LEDd7,LEDd5,LEDb2,LEDb3,LEDd3","LED_MX_6028R_Flipped","C5149201"
"MX_SK6812MINI-E","LEDc2,LEDe1,LEDe4,LEDe2,LEDc5,LEDe3,LEDa5,LEDa6,LEDc4,LEDa1,LEDe5,LEDa3,LEDa7,LEDc3,LEDc6,LEDa4,LEDa2","LED_MX_6028R","C5149201"
"MX_SW_HS","SWd4,SWb5,SWb3,SWb2,SWb4,SWa7,SWd7,SWd2,SWc2,SWc4,SWa2,SWa6,SWd6,SWa5,SWa1,SWc6,SWc3,SWd5,SWa3,SWa4,SWd3,SWc5,SWb6","SW_MX_HS_1u","C2803348"
"100n","C6,C22,C19,C7,C21,C23,C20,C12","C_0805","C495959"
"D","Dc6,Db6,Da5,Dc4,Da1,Db1,Dd5,Dd1,De1,De4,Db4,Da2,Dc5,Da6,Dc1,Db3,Da7,Dc3,De3,Dd4,Dc2,Dd3,Db2,Dd7,Da3,Db5,Dd2,De6,Dd6,Da4,De2","D_SOD-123","C81598"
"MX_SK6812MINI-E","LEDs15,LEDs12,LEDs7,LEDs2,LEDs8,LEDs9,LEDs1,LEDs4,LEDs3,LEDs14,LEDs5,LEDs10,LEDs16,LEDs6,LEDs13,LEDs17,LEDs11","sk6812side","C2890037"
"MX_SW_HS","SWe2,SWe3,SWe4,SWd1,SWe1","SW_MX_HS_1.25u","C2803348"
"USB_Link","J3","USB_C_Receptacle_HRO_TYPE-C-31-M-12","C165948"
"fb_0402_26ohm","FB2,FB4,FB3,FB1","R_0402_1005Metric","C668229"
"MX_SW_HS","SWcx1","SW_MX_HS_1.75u_stp","C2803348"
"MX_SK6812MINI-E","LEDd2,LEDd1,LEDc1","LED_MX_6028R_SOLO","C5149201"
"MX_SW_HS","SWdx1,SWe6","SW_MX_HS_2.25u","C2803348"
"2k2","R11","R_0603_1608Metric","C4190"
"LMV321","U6","SOT-23-5","C90297"
"cap_4.7uF_10v_0402","C15,C5","C_0402_1005Metric","C23733"
"Buzzer","LS1","Buzzer_Mallory_AST1109MLTRQ","C201047"
"r_75_0402_1p","R14,R6","R_0402_1005Metric","C25133"
"cap_100nF_16v_0402","C17,C11,C16,C14,C10,C2,C13","C_0402_1005Metric","C1525"
"MUN5311DW1T1G","Q3,Q1","SOT-363_SC-70-6_SC-88","C152542"
"cap_20pF_50v_0402","C8,C9","C_0402_1005Metric","C1554"
"AAP2967-33VIR1","U5","SOT-23-5","C370742"
"3A","F1","F1206","C89656"
"5.1k","R12","R_0805_2012Metric_Pad1.20x1.40mm_HandSolder","C104384"
"MX_SW_HS","SWc1","SW_MX_HS_1.75u","C2803348"
"r_470_0402_1p","R10","R_0402_1005Metric","C25117"
"cap_1uF_10v_0402","C1,C3","C_0402_1005Metric","C52923"
"W25Q128JVSIQ","U7","SOIC-8_5.23x5.23mm_P1.27mm","C97521"
"SMD-LED-WHITE_0402_","D4","LED_0402","C74342"
"1N4148","De5","D_SOD-523","C68948"
"r_10k_0402_1p","R8","R_0402_1005Metric","C25744"
"USB_Conn_2","J6","USB_C_Receptacle_HRO_TYPE-C-31-M-12","C165948"
"MB85RS64PNF-G-JNERE1","U4","SOP-8_3.9x4.9mm_P1.27mm","C8741"
"MX_SW_HS","SWb1","SW_MX_HS_1.5u","C2803348"
"SMD-CRYSTAL-8MHZ-20PF-10PPM_2P-5.0X3.2MM_","Y1","X2-SMD-5.0X3.2X1.3MM","C115962"
"LED","D3","LED_0603_1608Metric","C72041"
"SN74LV1T34DCKR","U8","SOT-353_SC-70-5","C78541"
"r_4.7k_0402_1p","R7","R_0402_1005Metric","C25900"
"TS3A27518ERTW","U1","WQFN-24-1EP_4x4mm_P0.5mm_EP2.6x2.6mm","C2651937"
"cap_10uF_10v_0402","C4","C_0402_1005Metric","C19702"
"Reset","SW1","SW_SPST_TL3342","C318884"
"AO3401A","Q2","SOT-23","C15127"
"r_100k_0402_1p","R9","R_0402_1005Metric","C25741"
"10u","C18","C_0805","C90544"
"USB_Conn_1","J2","USB_C_Receptacle_HRO_TYPE-C-31-M-12","C165948"
"USB_EXT","J1","USB_C_Receptacle_HRO_TYPE-C-31-M-12","C165948"
"1.5A","F2","F1206","C89655"

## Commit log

2023-02-14 Add left PCB
2023-03-07 Add right half. Not done with layout yet
2023-03-07 Before rotating switches and LEDs...
2023-03-11 Started rotating all switches; More progress on right half
2023-03-12 Left PCB done, for now at least
2023-03-12 Add all symbols and footprints to library
2023-03-12 Remove unused libs
2023-03-12 Add gitignore
2023-03-28 Right PCB routed. Needs DRC and some symbol fixing.
2023-04-01 Update right schematic symbols
2023-04-01 Export right footprints to libs
2024-03-15 Push latest, don't remember changes...
